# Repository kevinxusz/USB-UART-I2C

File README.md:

USB-UART-I2C
============

USB Interface for UART and I2C Tools.

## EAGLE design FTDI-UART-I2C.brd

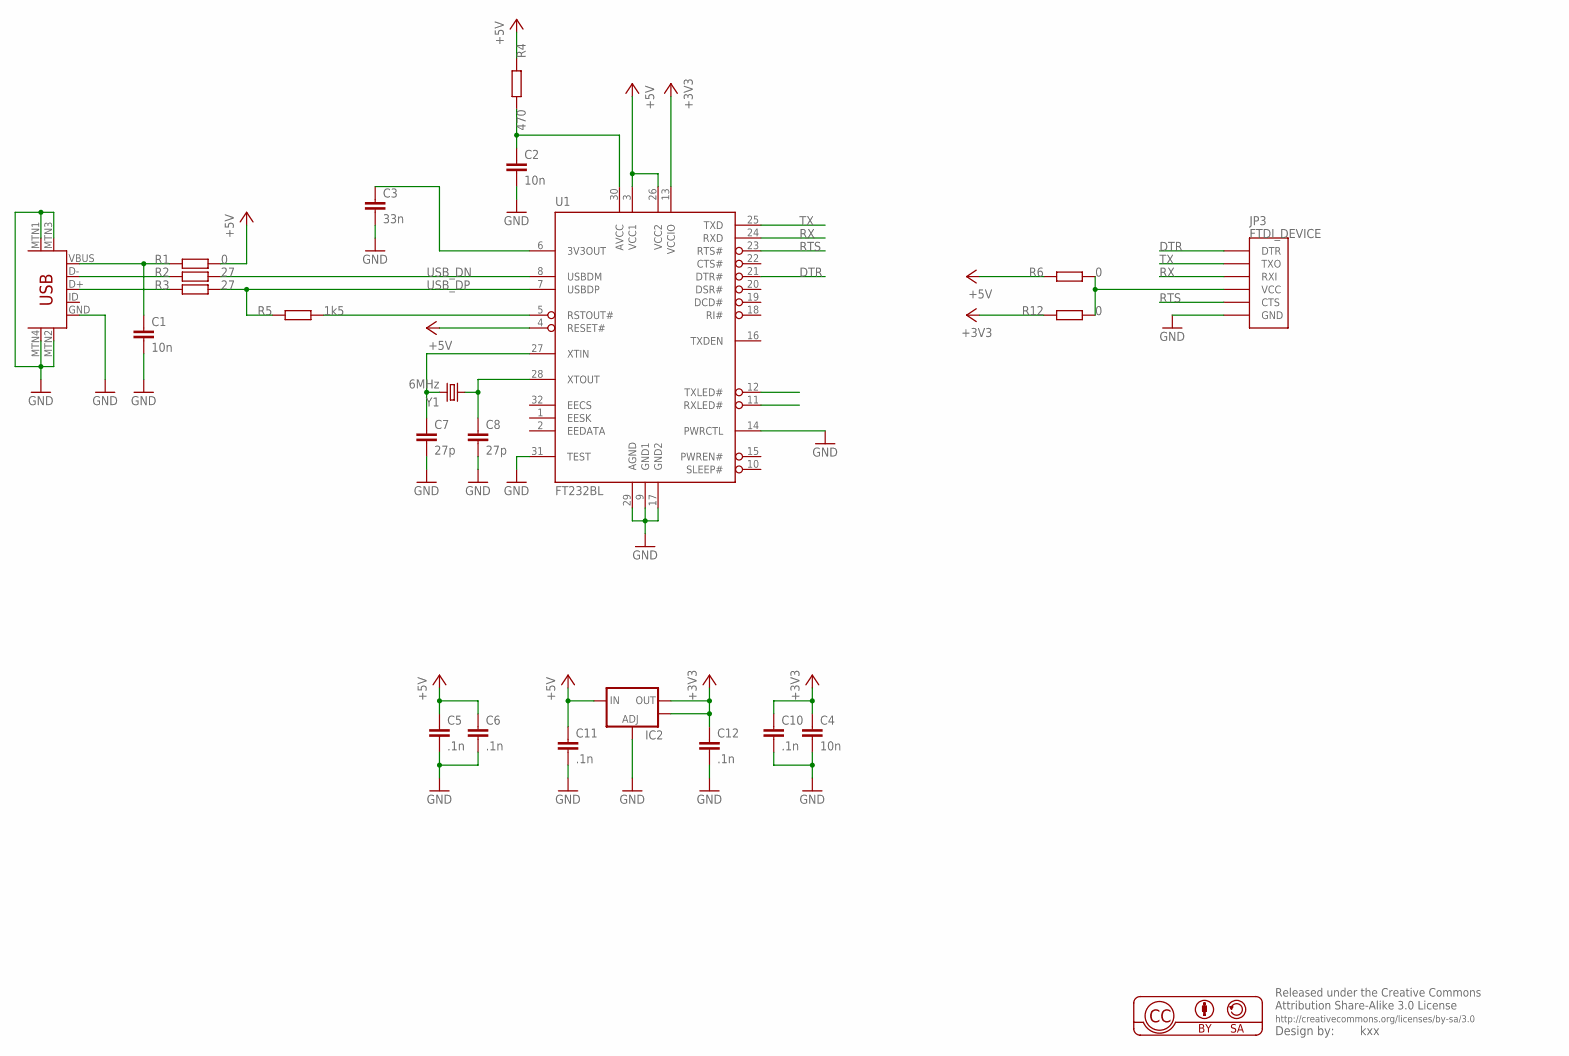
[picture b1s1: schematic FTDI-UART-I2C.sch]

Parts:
C1, C2, C4: 10n; C0805
C3: 33n; C0805
C5, C6, C10, C11, C12: .1n; C0805
C7, C8: 27p; C0805
IC2: V_REG_LM1117SOT223; SOT223
JP3: FTDI_DEVICE; FTDI_DEVICE_SIDE
R1, R6, R12: 0; R0603
R2, R3: 27; R0603
R4: 470; R0603
R5: 1k5; R0603
U1: FT232BL; LQFP32
U$2: USB-MINIB-5PIN; USB-MINIB
Y1: 6MHz; HC49U-V

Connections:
+3V3: C4.1, C10.1, C12.1, IC2.2 (OUT), IC2.4 (OUT), R12.1, U1.13 (VCCIO)
+5V: C5.1, C6.1, C11.1, IC2.3 (IN), R1.2, R4.1, R6.1, U1.3 (VCC1), U1.4 (RESET#), U1.26 (VCC2)
DTR: JP3.P$1 (DTR), U1.21 (DTR#)
GND: C1.2, C2.2, C3.2, C4.2, C5.2, C6.2, C7.2, C8.2, C10.2, C11.2, C12.2, IC2.1 (ADJ), JP3.P$6 (GND), U1.9 (GND1), U1.14 (PWRCTL), U1.17 (GND2), U1.29 (AGND), U1.31 (TEST), U$2.GND, U$2.MTN1 (MTN2), U$2.MTN2 (MTN3), U$2.MTN3 (MTN1), U$2.MTN4
unnamed: C1.1, R1.1, U$2.VBUS
unnamed: R2.1, U$2.D-
unnamed: R3.1, U$2.D+
unnamed: C2.1, R4.2, U1.30 (AVCC)
unnamed: C3.1, U1.6 (3V3OUT)
unnamed: C7.1, U1.27 (XTIN), Y1.2
unnamed: C8.1, U1.28 (XTOUT), Y1.1
unnamed: R5.2, U1.5 (RSTOUT#)
unnamed: JP3.P$4 (VCC), R6.2, R12.2
RTS: JP3.P$5 (CTS), U1.23 (RTS#)
RX: JP3.P$3 (RXI), U1.24 (RXD)
TX: JP3.P$2 (TXO), U1.25 (TXD)
USB_DN: R2.2, U1.8 (USBDM)
USB_DP: R3.2, R5.1, U1.7 (USBDP)

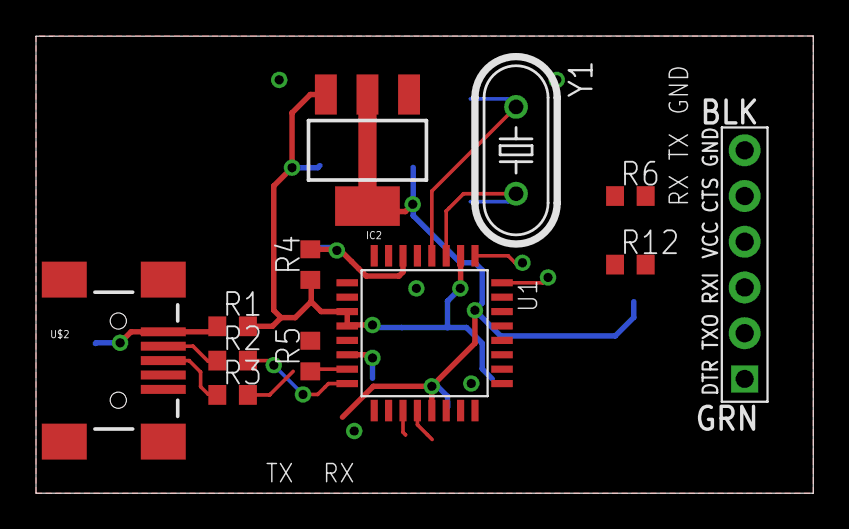
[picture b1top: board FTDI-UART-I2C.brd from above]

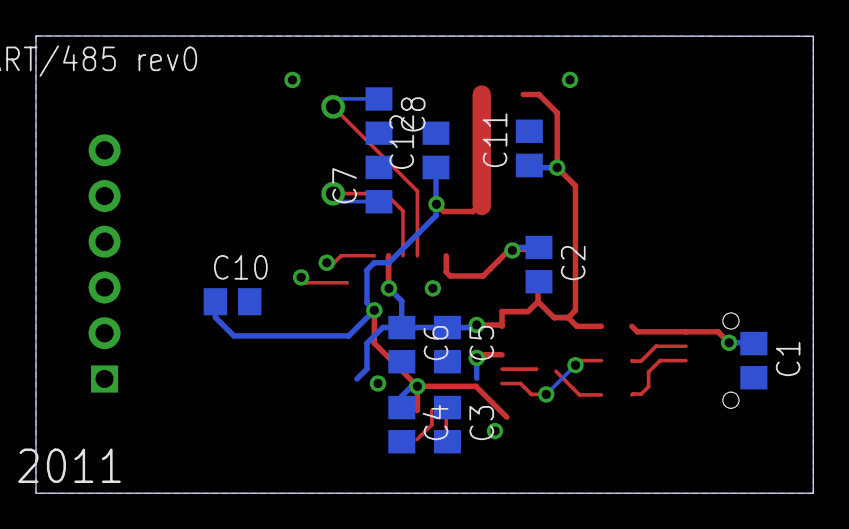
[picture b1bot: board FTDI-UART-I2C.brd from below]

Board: 2 copper layers, 43.2 x 25.4 mm, 23 parts (11 on the bottom side), 18 nets.

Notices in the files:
parts and their libraries:
SparkFun-Connectors: Licensing: CC v3.0 Share-Alike You are welcome to use this library for commercial purposes.
balto: Released under the Creative Commons
balto: http://creativecommons.org/licenses/by-sa/3.0
